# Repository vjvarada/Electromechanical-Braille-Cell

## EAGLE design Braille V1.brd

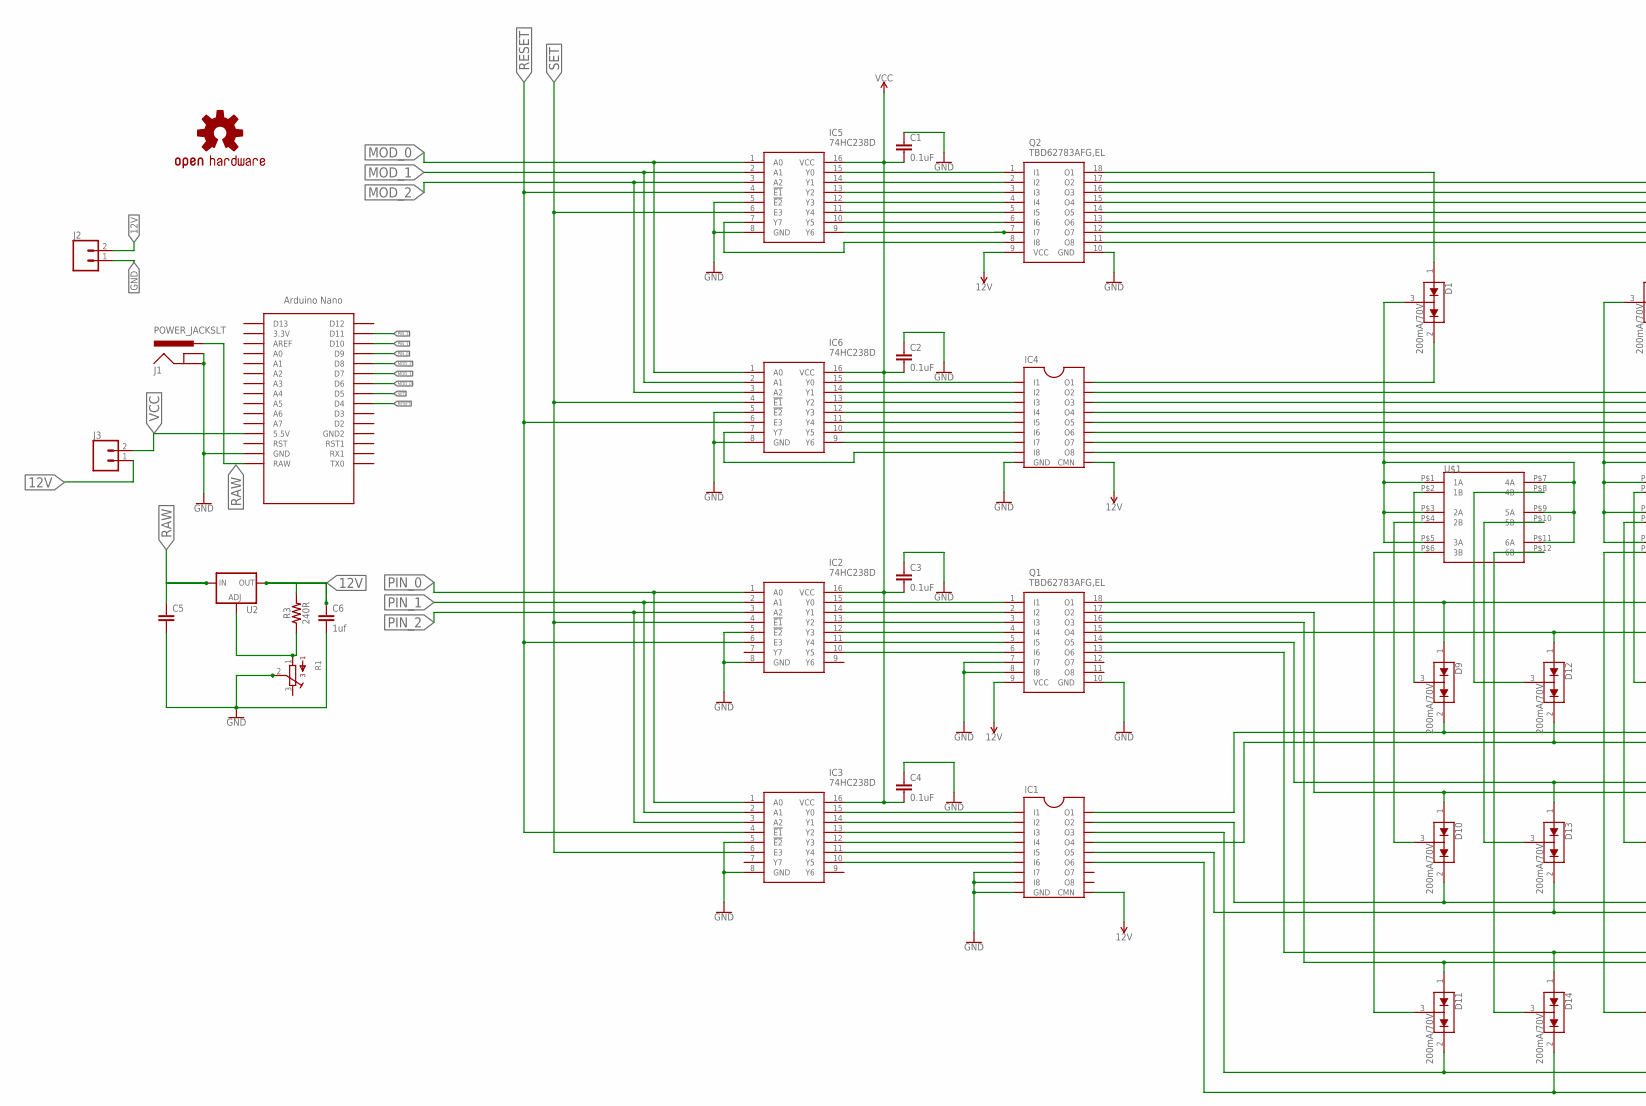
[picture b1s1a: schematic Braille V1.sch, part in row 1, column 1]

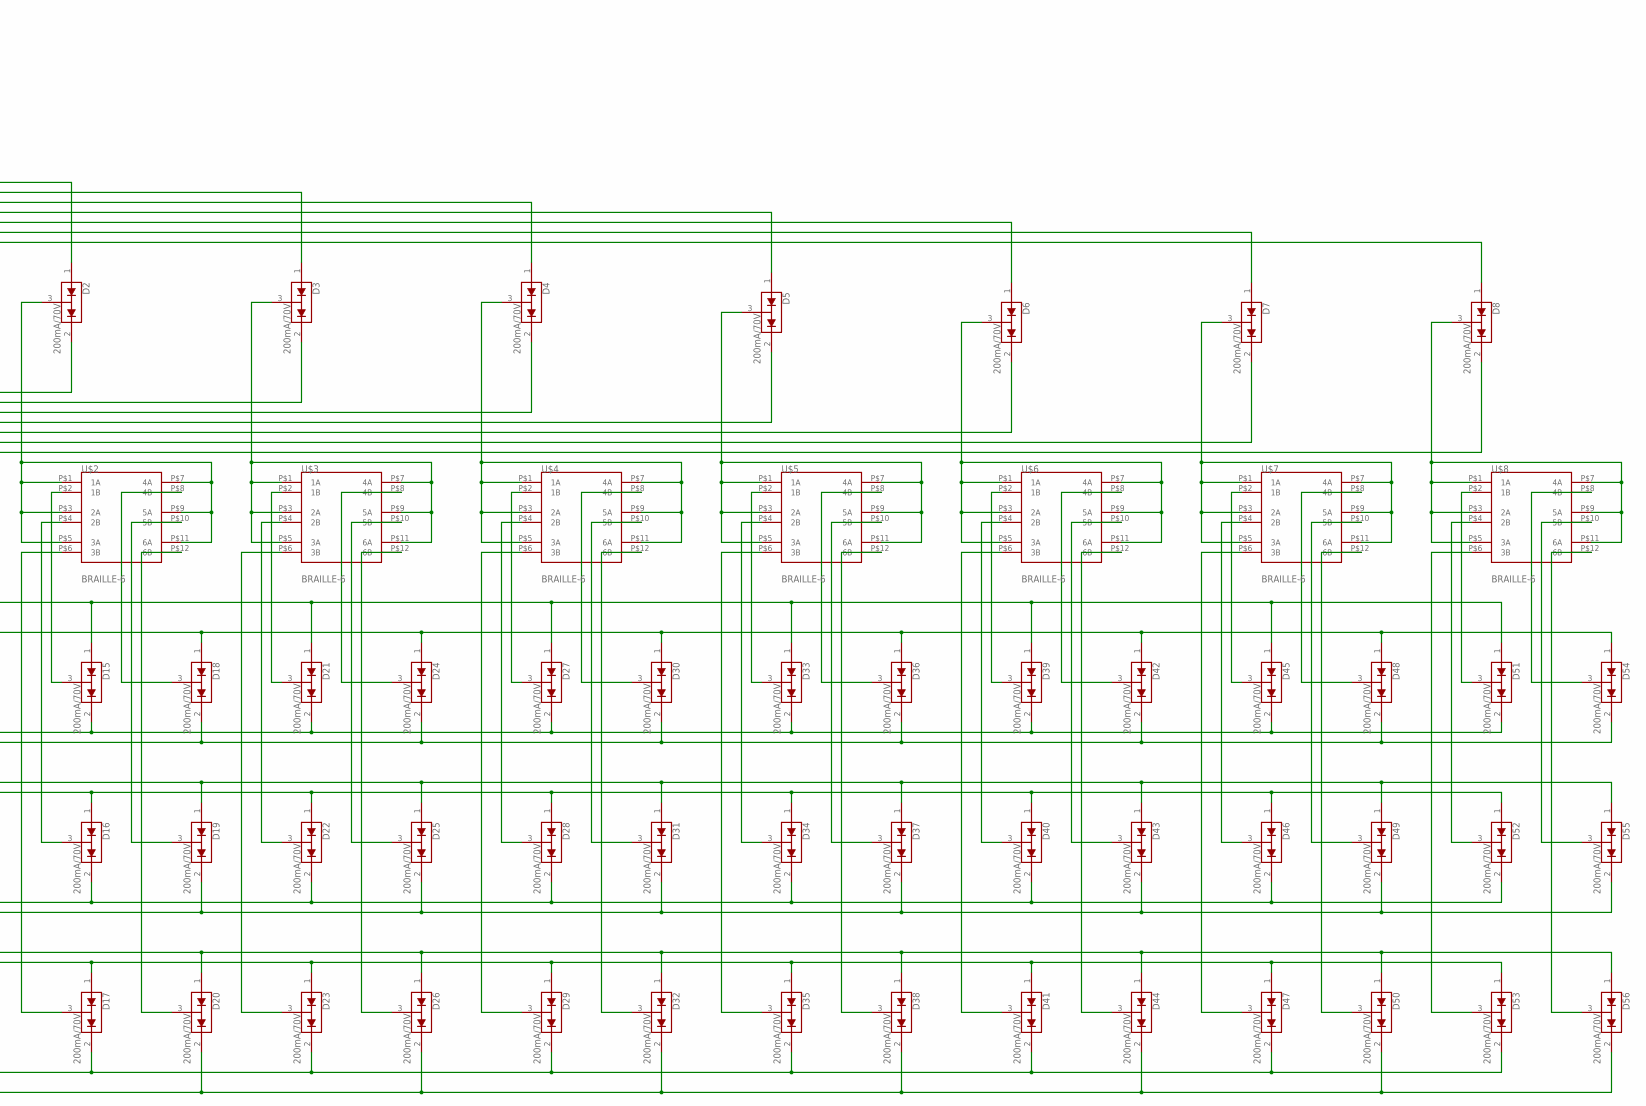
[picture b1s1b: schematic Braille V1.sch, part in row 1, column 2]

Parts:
C1, C2, C3, C4, C5: 0.1uF; 0603
C6: 1uf; 0603
D1, D2, D3, D4, D5, D6, D7, D8, D9, D10, D11, D12, D13, D14, D15, D16, D17, D18, D19, D20, D21, D22, D23, D24, D25, D26, D27, D28, D29, D30, D31, D32, D33, D34, D35, D36, D37, D38, D39, D40, D41, D42, D43, D44, D45, D46, D47, D48, D49, D50, D51, D52, D53, D54, D55, D56: 200mA/70V; SOT23-3
IC1, IC4: TD62083; SO18
IC2, IC3, IC5, IC6: 74HC238D; SOIC127P600X175-16N
J1: POWER_JACKSLT; POWER_JACK_SLOT
J2, J3: CONN_02; 1X02
LOGO1: OSHW-LOGOL-COPPER; OSHW-LOGO-L_COPPER
Q1, Q2: TBD62783AFG,EL; SOIC127P1030X245-18N
R1: 3362P
R3: 240R; 0603
U2: LM317; SOT223
U$1, U$2, U$3, U$4, U$5, U$6, U$7, U$8: BRAILLE-6
U$9: NANO

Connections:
12V: C6.1, IC1.10 (CMN), IC4.10 (CMN), J2.2, J3.1, Q1.9 (VCC), Q2.9 (VCC), R3.2, U2.2 (OUT)
GND: C1.1, C2.1, C3.1, C4.1, C5.2, C6.2, IC1.7 (I7), IC1.8 (I8), IC1.9 (GND), IC2.5 (!E2), IC2.8 (GND), IC3.5 (!E2), IC3.8 (GND), IC4.9 (GND), IC5.5 (!E2), IC5.8 (GND), IC6.5 (!E2), IC6.8 (GND), J1.GND@1 (GNDBREAK), J1.GND@2 (GND), J2.1, Q1.7 (I7), Q1.8 (I8), Q1.10 (GND), Q2.10 (GND), R1.2, U$9.GND
MOD_0: IC5.1 (A0), IC6.1 (A0), U$9.D6
MOD_1: IC5.2 (A1), IC6.2 (A1), U$9.D7
MOD_2: IC5.3 (A2), IC6.3 (A2), U$9.D8
unnamed: IC2.15 (Y0), Q1.1 (I1)
unnamed: IC2.14 (Y1), Q1.2 (I2)
unnamed: IC2.13 (Y2), Q1.3 (I3)
unnamed: IC2.12 (Y3), Q1.4 (I4)
unnamed: IC2.11 (Y4), Q1.5 (I5)
unnamed: IC2.10 (Y5), Q1.6 (I6)
unnamed: IC1.1 (I1), IC3.15 (Y0)
unnamed: IC1.2 (I2), IC3.14 (Y1)
unnamed: IC1.3 (I3), IC3.13 (Y2)
unnamed: IC1.4 (I4), IC3.12 (Y3)
unnamed: IC1.5 (I5), IC3.11 (Y4)
unnamed: IC5.15 (Y0), Q2.1 (I1)
unnamed: IC5.14 (Y1), Q2.2 (I2)
unnamed: IC5.13 (Y2), Q2.3 (I3)
unnamed: IC5.12 (Y3), Q2.4 (I4)
unnamed: IC5.11 (Y4), Q2.5 (I5)
unnamed: D1.1 (A1), Q2.18 (O1)
unnamed: IC4.1 (I1), IC6.15 (Y0)
unnamed: IC4.2 (I2), IC6.14 (Y1)
unnamed: IC4.3 (I3), IC6.13 (Y2)
unnamed: IC4.4 (I4), IC6.12 (Y3)
unnamed: IC4.5 (I5), IC6.11 (Y4)
unnamed: D2.1 (A1), Q2.17 (O2)
unnamed: IC5.10 (Y5), Q2.6 (I6)
unnamed: D3.1 (A1), Q2.16 (O3)
unnamed: IC5.9 (Y6), Q2.7 (I7)
unnamed: IC5.7 (Y7), Q2.8 (I8)
unnamed: IC4.8 (I8), IC6.7 (Y7)
unnamed: IC4.6 (I6), IC6.10 (Y5)
unnamed: IC4.7 (I7), IC6.9 (Y6)
unnamed: D4.1 (A1), Q2.15 (O4)
unnamed: IC1.6 (I6), IC3.10 (Y5)
unnamed: D5.1 (A1), Q2.14 (O5)
unnamed: D6.1 (A1), Q2.13 (O6)
unnamed: D7.1 (A1), Q2.12 (O7)
unnamed: D8.1 (A1), Q2.11 (O8)
unnamed: D1.2 (C2), IC4.18 (O1)
unnamed: D9.3 (COM), U$1.P$2 (1B)
unnamed: D2.2 (C2), IC4.17 (O2)
unnamed: D3.3 (COM), U$3.P$1 (1A), U$3.P$3 (2A), U$3.P$5 (3A), U$3.P$7 (4A), U$3.P$9 (5A), U$3.P$11 (6A)
unnamed: D4.3 (COM), U$4.P$1 (1A), U$4.P$3 (2A), U$4.P$5 (3A), U$4.P$7 (4A), U$4.P$9 (5A), U$4.P$11 (6A)
unnamed: D5.3 (COM), U$5.P$1 (1A), U$5.P$3 (2A), U$5.P$5 (3A), U$5.P$7 (4A), U$5.P$9 (5A), U$5.P$11 (6A)
unnamed: D6.3 (COM), U$6.P$1 (1A), U$6.P$3 (2A), U$6.P$5 (3A), U$6.P$7 (4A), U$6.P$9 (5A), U$6.P$11 (6A)
unnamed: D7.3 (COM), U$7.P$1 (1A), U$7.P$3 (2A), U$7.P$5 (3A), U$7.P$7 (4A), U$7.P$9 (5A), U$7.P$11 (6A)
unnamed: D8.3 (COM), U$8.P$1 (1A), U$8.P$3 (2A), U$8.P$5 (3A), U$8.P$7 (4A), U$8.P$9 (5A), U$8.P$11 (6A)
unnamed: D10.3 (COM), U$1.P$4 (2B)
unnamed: D11.3 (COM), U$1.P$6 (3B)
unnamed: D12.3 (COM), U$1.P$8 (4B)
unnamed: D13.3 (COM), U$1.P$10 (5B)
unnamed: D14.3 (COM), U$1.P$12 (6B)
unnamed: D21.3 (COM), U$3.P$2 (1B)
unnamed: D10.1 (A1), D16.1 (A1), D22.1 (A1), D28.1 (A1), D34.1 (A1), D40.1 (A1), D46.1 (A1), D52.1 (A1), Q1.17 (O2)
unnamed: D11.1 (A1), D17.1 (A1), D23.1 (A1), D29.1 (A1), D35.1 (A1), D41.1 (A1), D47.1 (A1), D53.1 (A1), Q1.16 (O3)
unnamed: D12.1 (A1), D18.1 (A1), D24.1 (A1), D30.1 (A1), D36.1 (A1), D42.1 (A1), D48.1 (A1), D54.1 (A1), Q1.15 (O4)
unnamed: D27.3 (COM), U$4.P$2 (1B)
unnamed: D33.3 (COM), U$5.P$2 (1B)
unnamed: D9.2 (C2), D15.2 (C2), D21.2 (C2), D27.2 (C2), D33.2 (C2), D39.2 (C2), D45.2 (C2), D51.2 (C2), IC1.18 (O1)
unnamed: D39.3 (COM), U$6.P$2 (1B)
unnamed: D11.2 (C2), D17.2 (C2), D23.2 (C2), D29.2 (C2), D35.2 (C2), D41.2 (C2), D47.2 (C2), D53.2 (C2), IC1.16 (O3)
unnamed: D12.2 (C2), D18.2 (C2), D24.2 (C2), D30.2 (C2), D36.2 (C2), D42.2 (C2), D48.2 (C2), D54.2 (C2), IC1.15 (O4)
unnamed: D13.2 (C2), D19.2 (C2), D25.2 (C2), D31.2 (C2), D37.2 (C2), D43.2 (C2), D49.2 (C2), D55.2 (C2), IC1.14 (O5)
unnamed: D14.2 (C2), D20.2 (C2), D26.2 (C2), D32.2 (C2), D38.2 (C2), D44.2 (C2), D50.2 (C2), D56.2 (C2), IC1.13 (O6)
unnamed: D15.3 (COM), U$2.P$2 (1B)
unnamed: D16.3 (COM), U$2.P$4 (2B)
unnamed: D17.3 (COM), U$2.P$6 (3B)
unnamed: D18.3 (COM), U$2.P$8 (4B)
unnamed: D19.3 (COM), U$2.P$10 (5B)
unnamed: D20.3 (COM), U$2.P$12 (6B)
unnamed: D28.3 (COM), U$4.P$4 (2B)
unnamed: D22.3 (COM), U$3.P$4 (2B)
unnamed: D23.3 (COM), U$3.P$6 (3B)
unnamed: D24.3 (COM), U$3.P$8 (4B)
unnamed: D25.3 (COM), U$3.P$10 (5B)
unnamed: D26.3 (COM), U$3.P$12 (6B)
unnamed: D45.3 (COM), U$7.P$2 (1B)
unnamed: D10.2 (C2), D16.2 (C2), D22.2 (C2), D28.2 (C2), D34.2 (C2), D40.2 (C2), D46.2 (C2), D52.2 (C2), IC1.17 (O2)
unnamed: D51.3 (COM), U$8.P$2 (1B)
unnamed: D1.3 (COM), U$1.P$1 (1A), U$1.P$3 (2A), U$1.P$5 (3A), U$1.P$7 (4A), U$1.P$9 (5A), U$1.P$11 (6A)
unnamed: D2.3 (COM), U$2.P$1 (1A), U$2.P$3 (2A), U$2.P$5 (3A), U$2.P$7 (4A), U$2.P$9 (5A), U$2.P$11 (6A)
unnamed: D29.3 (COM), U$4.P$6 (3B)
unnamed: D30.3 (COM), U$4.P$8 (4B)
unnamed: D3.2 (C2), IC4.16 (O3)
unnamed: D13.1 (A1), D19.1 (A1), D25.1 (A1), D31.1 (A1), D37.1 (A1), D43.1 (A1), D49.1 (A1), D55.1 (A1), Q1.14 (O5)
unnamed: D14.1 (A1), D20.1 (A1), D26.1 (A1), D32.1 (A1), D38.1 (A1), D44.1 (A1), D50.1 (A1), D56.1 (A1), Q1.13 (O6)
unnamed: D4.2 (C2), IC4.15 (O4)
unnamed: D5.2 (C2), IC4.14 (O5)
unnamed: D6.2 (C2), IC4.13 (O6)
unnamed: D7.2 (C2), IC4.12 (O7)
unnamed: D8.2 (C2), IC4.11 (O8)
unnamed: D31.3 (COM), U$4.P$10 (5B)
unnamed: D32.3 (COM), U$4.P$12 (6B)
unnamed: R1.1, R3.1, U2.1 (ADJ)
unnamed: D34.3 (COM), U$5.P$4 (2B)
unnamed: D35.3 (COM), U$5.P$6 (3B)
unnamed: D36.3 (COM), U$5.P$8 (4B)
unnamed: D37.3 (COM), U$5.P$10 (5B)
unnamed: D38.3 (COM), U$5.P$12 (6B)
unnamed: D40.3 (COM), U$6.P$4 (2B)
unnamed: D41.3 (COM), U$6.P$6 (3B)
unnamed: D42.3 (COM), U$6.P$8 (4B)
unnamed: D43.3 (COM), U$6.P$10 (5B)
unnamed: D44.3 (COM), U$6.P$12 (6B)
unnamed: D46.3 (COM), U$7.P$4 (2B)
unnamed: D47.3 (COM), U$7.P$6 (3B)
unnamed: D48.3 (COM), U$7.P$8 (4B)
unnamed: D49.3 (COM), U$7.P$10 (5B)
unnamed: D50.3 (COM), U$7.P$12 (6B)
unnamed: D52.3 (COM), U$8.P$4 (2B)
unnamed: D53.3 (COM), U$8.P$6 (3B)
unnamed: D54.3 (COM), U$8.P$8 (4B)
unnamed: D55.3 (COM), U$8.P$10 (5B)
unnamed: D56.3 (COM), U$8.P$12 (6B)
unnamed: D9.1 (A1), D15.1 (A1), D21.1 (A1), D27.1 (A1), D33.1 (A1), D39.1 (A1), D45.1 (A1), D51.1 (A1), Q1.18 (O1)
PIN_0: IC2.1 (A0), IC3.1 (A0), U$9.D9
PIN_1: IC2.2 (A1), IC3.2 (A1), U$9.D10
PIN_2: IC2.3 (A2), IC3.3 (A2), U$9.D11
RAW: C5.1, J1.PWR, U2.3 (IN), U$9.RAW
RESET: IC2.6 (E3), IC3.4 (!E1), IC5.4 (!E1), IC6.6 (E3), U$9.D4
SET: IC2.4 (!E1), IC3.6 (E3), IC5.6 (E3), IC6.4 (!E1), U$9.D5
VCC: C1.2, C2.2, C3.2, C4.2, IC2.16 (VCC), IC3.16 (VCC), IC5.16 (VCC), IC6.16 (VCC), J3.2, U$9.5V (5.5V)

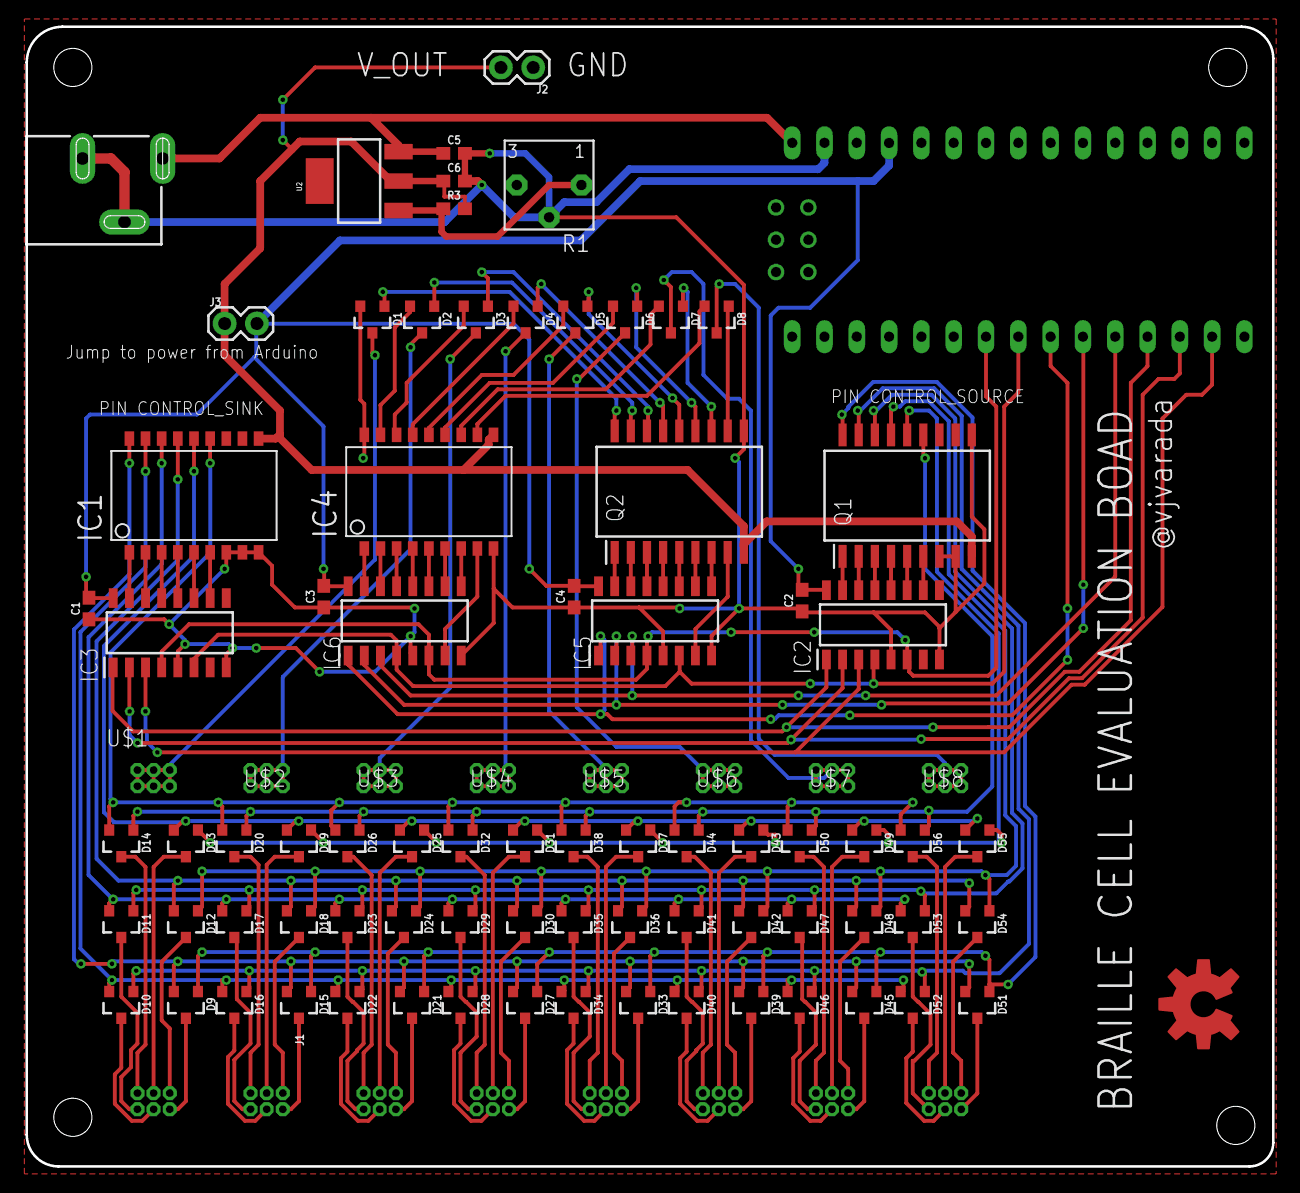
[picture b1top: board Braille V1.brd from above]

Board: 2 copper layers, 98.0 x 89.6 mm, 86 parts (0 on the bottom side), 125 nets.

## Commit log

2023-09-14 Updated Test Point
2023-09-14 Braille Cell added

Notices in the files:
parts and their libraries:
SparkFun-DiscreteSemi: Licensing: Creative Commons ShareAlike 4.0 International - https://creativecommons.org/licenses/by-sa/4.0
